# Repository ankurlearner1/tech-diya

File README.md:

# tech-diya
My first custom PCB design for Tech-Diya using KiCad 9.0
# 🔌 My First PCB Design – KiCad Journey Begins

This repository contains my **first-ever PCB design**, created using **KiCad** 🎉.  
It was a fun and foundational experience exploring the world of PCB design — from schematics to layout.  
While this board is *functionally complete* and includes all the necessary files, it is **not yet fully optimized** in terms of routing, layout, and component choice.

---

## ⚠️ Note
> **This design is not intended for real-world printing (yet).**  
> Although it includes Gerber files and looks "print-ready", it should be considered **hypothetical** at this stage.  
> Future revisions will focus on:
> - Design rule optimization  
> - Component placement improvements  
> - Manufacturability enhancements

---

## 📂 Project Structure
MyFirstPCB/
├── 📘 README.md           → Project overview and details
├── 📂 schematic/          → KiCad schematic files (.kicad_sch)
│
├── 📂 pcb_layout/         → KiCad PCB layout files (.kicad_pcb)
│
├── 📂 gerber/             → Gerber & drill files for fabrication
│   ├── .gbr               → Gerber layer files
│   └── .drl               → Drill file
│
├── 📂 BOM/                → Bill of Materials (CSV or Excel)
│
└── 📂 images/             → 2D/3D board previews and screenshots

---

## 🛠 Tools Used
- [KiCad 9.0](https://kicad.org/) for schematic + PCB layout  
- Online preview tools for 3D renders and Gerber inspection

---

## 📸 Preview
The circuit digram that i have used !!
> 
> 
>

> 
> 

---

## ❓ Questions & Feedback
If you have any questions, suggestions, or feedback about the design or how I can improve, feel free to open an [Issue](https://github.com/ankurlearner1/MyFirstPCB/issues) or contact me directly.  
I’m learning, experimenting, and always open to improvement.

---

## 🔄 Future Plans
- Improve trace widths and spacing
- Add silkscreen details
- Perform DRC (Design Rule Check) validation
- Generate fabrication-ready files

---

## 📝 License
This project is open-source under the **MIT License** – feel free to learn from it, but use it responsibly.

---

**Thanks for checking out my journey into the world of hardware! 🚀**

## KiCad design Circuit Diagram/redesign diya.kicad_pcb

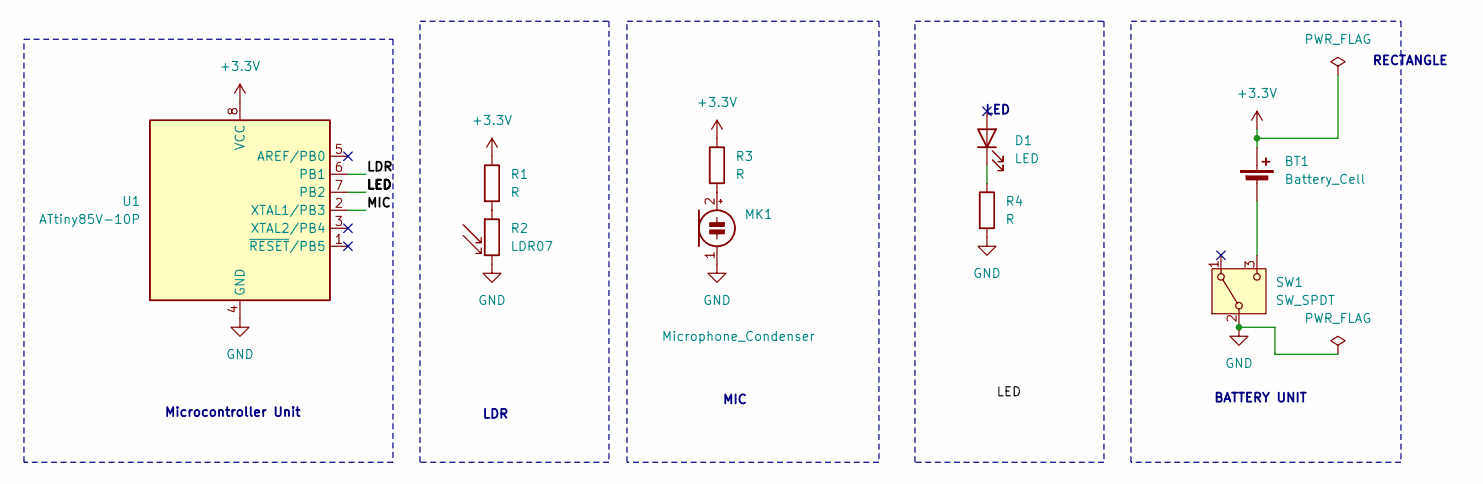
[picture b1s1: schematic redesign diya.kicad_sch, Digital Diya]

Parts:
BT1: Battery_Cell; BatteryHolder_ComfortableElectronic_CH273-2450_1x2450
D1: LED; LED_D3.0mm
MK1: Microphone_Condenser; PinHeader_1x02_P2.54mm_Vertical
R1, R3, R4: R; R_Axial_DIN0207_L6.3mm_D2.5mm_P15.24mm_Horizontal
R2: LDR07; R_LDR_5.1x4.3mm_P3.4mm_Vertical
SW1: SW_SPDT; SW_Slide_SPDT_Angled_CK_OS102011MA1Q
U1: ATtiny85V-10P; DIP-8_W7.62mm

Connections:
+3.3V: BT1.1 (+), R1.1, R3.1, U1.8 (VCC)
/LDR: U1.6 (PB1)
/LED: U1.7 (PB2)
/MIC: U1.2 (XTAL1/PB3)
GND: MK1.1 (-), R2.2, R4.2, SW1.2 (B), U1.4 (GND)
unnamed: BT1.2 (-), SW1.3 (C)
unnamed: D1.1 (K), R4.1
unnamed: MK1.2 (+), R3.2
unnamed: R1.2, R2.1

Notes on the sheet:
MIC
LED
BATTERY UNIT
Microcontroller Unit
LDR
RECTANGLE

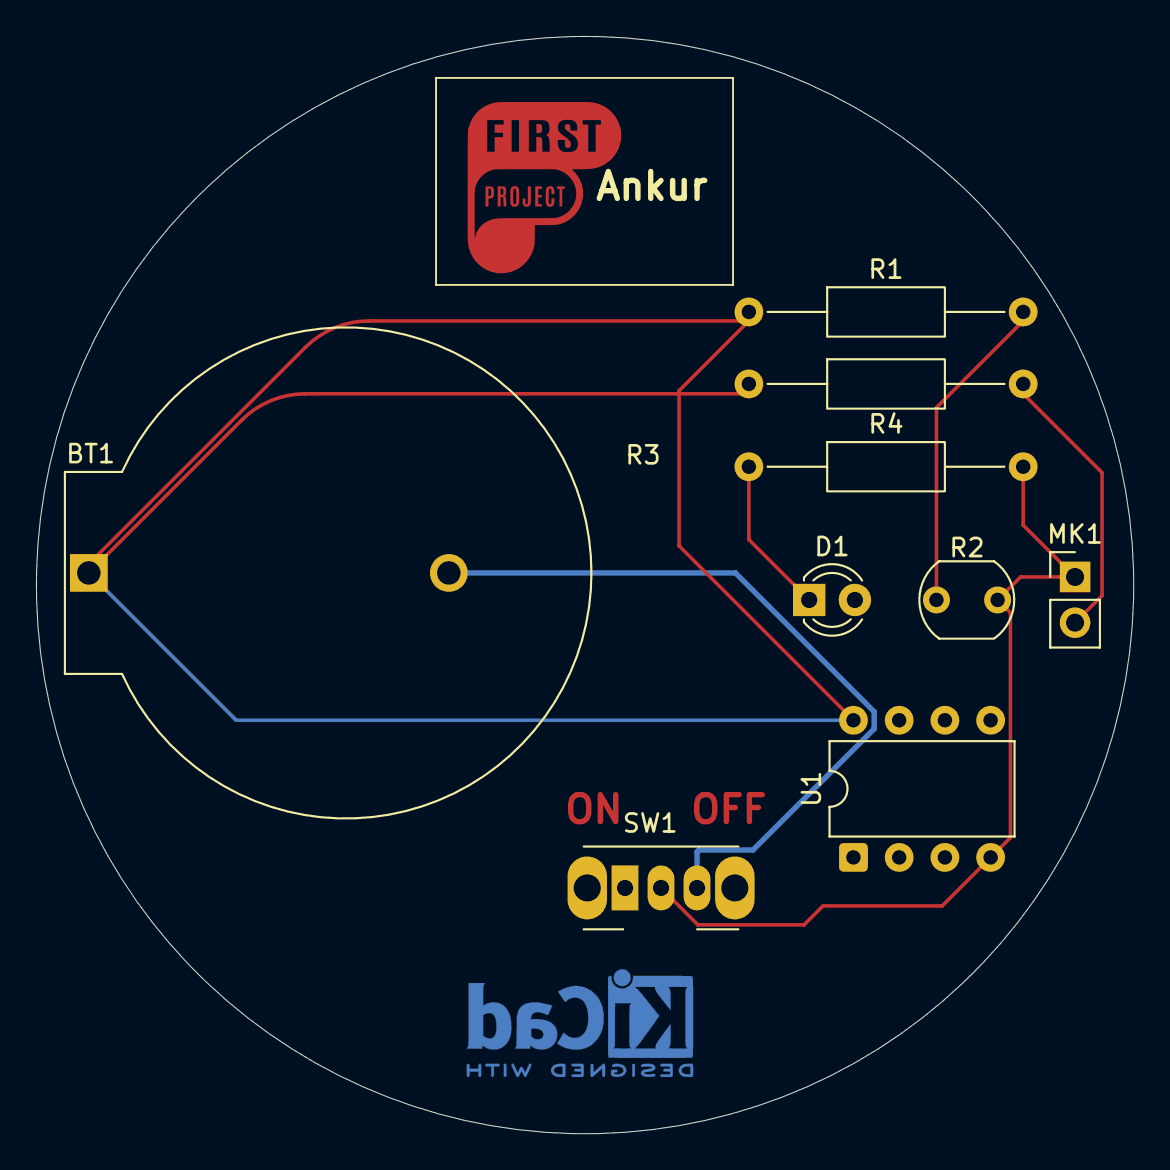
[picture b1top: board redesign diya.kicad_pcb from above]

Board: 2 copper layers, 61.0 x 61.0 mm, 10 parts (0 on the bottom side), 6 nets.

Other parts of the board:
Ankur: LOGO

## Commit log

2025-06-23 Create schemtic digram
2025-06-23 Rename schemtic digram to Schematic digram
2025-06-23 Schematic.keep
2025-06-23 Rename Schematic digram to Schematic digram.keep
2025-06-23 Add files via upload
    This the pcb layout that i have design using my schematic diagram
2025-06-23 Add files via upload
    Added Gerber files generated from my first KiCad PCB design.
    These files include the copper layers, silkscreen, solder mask, and drill files.
    Please note: This board is not fully optimized and has not been tested for manufacturing — use for reference only.
2025-06-23 Create LICENSE
2025-06-23 Add files via upload
    Added board layout and 3D rendered images to the images/ folder.
    These visuals help in understanding the PCB design at a glance.
    Useful for documentation, presentation, and future reference.
2025-06-23 Create Special Thanks
